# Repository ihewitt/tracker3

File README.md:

# Tracker III.2
A BG96 and NRF52840 based GPS tracker

The history for this design can be found on a series of posts: [Tracking running](https://blog.ivor.org/2020/10/tracking-running-part-2.html) [RAK track](https://blog.ivor.org/2022/02/between-rak-and-sweet-place.html) [Tracker two](https://blog.ivor.org/2022/03/trackertwo.html), the full details for this build are at [T3 Rise of the machines](https://blog.ivor.org/2024/08/t3-rise-of-machines.html)

Latest schematic [here](schematic.pdf), component layout [here](layout.pdf), Bill of materials [here](tracker-bom.csv)

Main functional features on the board are highlighted here:

### USB connection
I changed to a USB-C connector, and the USB connection can be switched between the NRF and BG96 chips, most of the time the NRF will be useful but if you need/want to diagnose the GPS data directly or update the BG96 firmware then you can move jumpers.

### Charger
I changed the charger design to include a load share design and a power regulator with a "reverse current" protection shown on the schematic:

When USB power is applied and the TP4056 starts charging, the MOSFET IC2 detaches the battery from the load and the power to the board is taken from the regulator U9.
When the USB power is removed and the battery (VBAT_IN) is the source then the MOSFET lets the power run through to VBAT_OUT directly, the reverse current protection on U9 prevents it returning to the 5v line.

### Regulators
The board internally runs all devices and data lines at 1.8v but level shifts these for external interfacing to 3.3v.

### IO Ports
Two qwiik compatible connectors provide 3.3v I2C and general purpose IO lines.

### Fuel Gauge
A MAX17048 fuel gauge chip is included to give an accurate and reliable power level info.

### Flash
Onboard 8Gb Flash module, I'm still on the fence whether to replace this with an SDcard slot instead.

### Temp & Humidity
Since I had a space on the board and it was next to the I2C lines, I changed my mind and decided to include a SHTC3 temperature and humidity chip. I found the temperature in tracker2 wasn't particularly useful so instead used an external ANT sensor, but the humidity was handy.

### Button connectors
Four GPIO lines are exposed alongside a ground line to make it easy to add a set of buttons.

# Render
The render view in KiCad is handy to check the layout looks sane and makes sense:

A picture of a nearly final prototype up and running:

## Build Notes
The build is a single sided board so quite straightforward to manufacture, although there are a few options to make it simpler.

Firstly optional parts, the fuel gauge can be omitted just skip U4 and C17, the pull-ups are still needed though for working I2C.
Similarly the temperature sensor can be skipped, omit U10 and C35.
The flash isn't absolutely necessary, but it's an easy to solder part and it's really quite useful.
The entire charge circuit can be omitted if preferred and the battery charged externally, but again these aren't complicated parts to solder. 

Just skip the parts marked in green and connect VBAT_IN to VBAT_OUT (in red)

Another option is to use a BG95 instead of the BG96, since they are software and pin compatible, the BG95 was considerably cheaper for a while although prices seem to have returned to sanity now.
The downside of the BG95 is that it can't operate GPS and GSM simultaneously, not a huge issue with a 1 or 5 minute upload.

### Difficult parts
Next up, difficult parts to solder.... the fuel gauge U4, and the ESD's U2 and U5 have very close contacts, these can bridge even with hotplate soldering so need inspecting although the pins can be easily fixed with the touch of a fine soldering iron since the pins are visible at the edges. Similary the USB-C socket can be trouble and needs inspection.

### Soldering
It's a good idea to use low temperature solder since a full temperature reflow will also reflow the internals of the BG96 and Holyiot modules. Another possibility would be to get the board manufactured by someone else (or flowed yourself) in two stages, initially just all the components *except* the two modules using standard temperature solder. Then after the board is manufactured, apply low temp paste for the BG96 and Holyiot for a second low-temp reflow.

### Software
As a starting point the software for the "RAKtrack" can be used after changing the pin numbers (the Pin numbers for v3 are in [gpiopins.h](gpiopins.h)). When the IVRtrack code is polished I'll update and add to this github also. 

For RAK track, the website server software is [here](https://github.com/ihewitt/gps-server). and the firmware for the rak board is [here](https://github.com/ihewitt/raktrack).

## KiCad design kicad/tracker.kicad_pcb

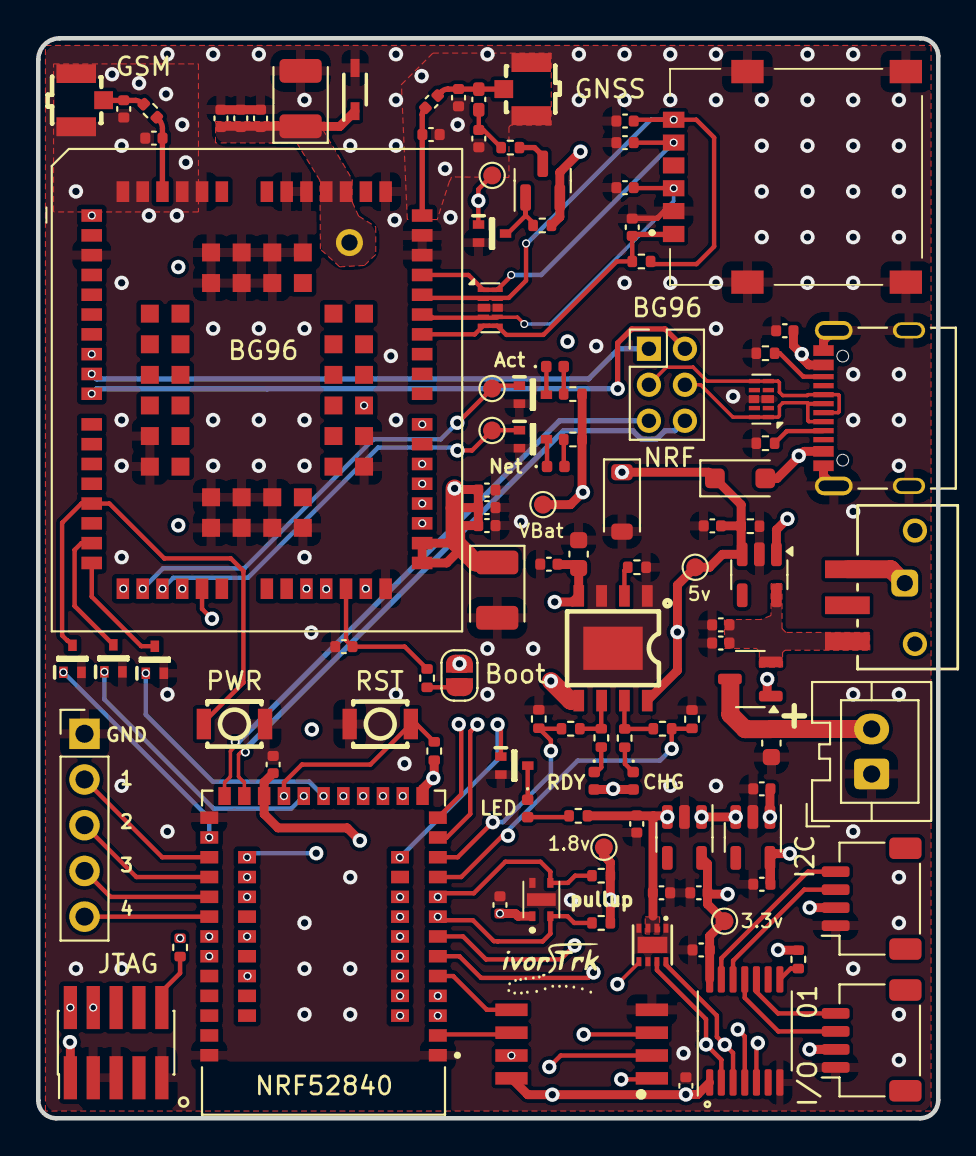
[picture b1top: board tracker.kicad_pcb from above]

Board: 4 copper layers, 50.0 x 60.0 mm, 111 parts (0 on the bottom side), 89 nets.

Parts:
ANT1, ANT2: U.FL-R-SMT-1_10_; RF-SMD_FRF05002-JSS103M
C1: 4.7uF; C_0402_1005Metric
C2: 10nF; C_0402_1005Metric
C3, C13, C14, C17, C18, C19, C29, C30, C31, C32, C33, C35: 0.1uF; C_0402_1005Metric
C4: 100pF; C_0402_1005Metric
C5, C6, C7, C11, C12: 33pF; C_0402_1005Metric
C8, C26, C27, C28: nc; C_0402_1005Metric
C9, C10: 10pF; C_0402_1005Metric
C15, C16: 100uF; CP_EIA-3528-21_Kemet-B
C20, C34: 10uF; C_0603_1608Metric
C21, C22, C23, C24, C25: 1uF; C_0402_1005Metric
D1: LED Orange; LED_0402_1005Metric
D2: LED Blue; LED_0402_1005Metric
D3: MBR140SFT1G; D_SOD-123F
D4: LBZT52B5V6T1G; D_SOD-123
D5: LED Red; LED_0402_1005Metric
D11: Green; LED_0402_1005Metric
D12: Red; LED_0402_1005Metric
H1, H4: Pad
IC1: IS25WP064A-JBLE; SOIC-8_L5.3-W5.3-P1.27-LS7.9-BL
IC2: DMP1045U-7; SOT-23-3
J1: Conn_01x05_Pin; PinHeader_1x05_P2.54mm_Vertical
J2, J6: I2C; JST_SH_SM04B-SRSS-TB_1x04-1MP_P1.00mm_Horizontal
J3: JTAG; PinHeader_2x05_P1.27mm_Vertical_SMD
J4: SMN-305; SMN305
J7: BAT_CON; JST_XA_B02B-XASK-1_1x02_P2.50mm_Vertical
J9: USBC; 12402012E212A
JP2: USB Select; PinHeader_2x03_P2.00mm_Vertical
L1: 47nh; L_0402_1005Metric_Pad0.77x0.64mm_HandSolder
Q1, Q5, Q6, Q7, Q8, Q9: DTC043ZEBTL; SOTFL50P160X85-3N
Q10: DTC143ZEBTL; SOTFL50P160X85-3N
Q11: IRLML6401; SOT-23
R1, R3, R4, R10, R16, R17: 10k; R_0402_1005Metric
R2, R9, R12, R13: 4.7k; R_0402_1005Metric
R5, R6: 5.1k; R_0402_1005Metric
R7: 100k; R_0402_1005Metric
R8, R15, R23, R24: 1k; R_0402_1005Metric
R11: 10; R_0402_1005Metric
R14, R18: 0; R_0402_1005Metric
R19, R20: 2k; R_0402_1005Metric
R22: 1.2k; R_0402_1005Metric
SW1: PWR; KEY-SMD_B3U-1000PM
SW2: RESET; KEY-SMD_B3U-1000PM
SW3: SW_SPDT; SW3_CSS-1210TB_NDC
TP1: TestPoint_2Pole; SolderJumper-2_P1.3mm_Open_RoundedPad1.0x1.5mm
TP3, TP4, TP5, TP6, TP7, TP8, TP9: TestPoint; TestPoint_Pad_D1.0mm
U1: HOLYIOT-18010-NRF52840; XCVR_HOLYIOT-18010-NRF52840
U2, U5: D3V3XA4B10LP; Diodes_UDFN-10_1.0x2.5mm_P0.5mm
U3: BG96; Quectel_BG96
U4: MAX17048; DFN-8_L2.0-W2.0-P0.50-BL-EP
U6: TP4056; ESOP-8_L4.9-W3.9-P1.27-LS6.0-BL-EP
U7: AP2127K-3.3; SOT-23-5
U8: AP2127K-1.8; SOT-23-5
U9: RP173N421B; SOT-23-5
U10: SHTC3
U11: TXS0104PWR; TSSOP-14_4.4x5mm_P0.65mm
Z1: MM3Z5V1ST1G; SOD2512X110N

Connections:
+3.3V: C23.1, C30.1, J2.2, J6.2, TP5.1, U7.5 (VOUT), U11.14 (VCCB)
+5V: C19.2, C32.2, C34.1, D3.1 (K), D4.1 (K), D11.2 (A), D12.2 (A), IC2.1 (G), R7.1, TP6.1, U3.8 (USB_VBUS), U6.4 (VCC), U6.8 (CE), U9.1 (VIN), U9.3 (EN)
BAT_ALRT: U1.40 (P0.25), U4.5 (~ALRT)
BG96_AP_READY: U1.49 (P0.24), U3.19 (AP_READY)
BG96_CTS: U1.15 (P0.07), U3.36 (CTS)
BG96_DTR: U1.16 (P1.09), U3.30 (DTR)
BG96_NETLIGHT: Q9.1 (B), TP8.1, U3.21 (NETLIGHT)
BG96_PSM: U1.43 (P0.27), U3.1 (PSM_IND)
BG96_PWRKEY: Q8.1 (B), U1.26 (P0.22)
BG96_PWRKEY_N: Q8.3 (C), SW1.2 (B), U3.15 (PWRKEY)
BG96_RESET: Q7.1 (B), U1.20 (P0.19)
BG96_RESET_N: Q7.3 (C), U3.17 (~RESET)
BG96_RI: U1.18 (P0.23), U3.39 (RI)
BG96_RTS: U1.17 (P0.12), U3.37 (RTS)
BG96_RX: U1.12 (P0.04), U3.34 (RXD)
BG96_RX2: U1.44 (P0.08), U3.23 (DBG_TXD)
BG96_RX3: U1.54 (P0.13), U3.28 (UART3_RXD)
BG96_STATUS: Q1.1 (B), TP7.1, U1.41 (P0.11), U3.20 (STATUS)
BG96_TX: U1.13 (P0.05), U3.35 (TXD)
BG96_TX2: U1.42 (P1.08), U3.22 (DBG_RXD)
BG96_TX3: U1.55 (P0.16), U3.27 (UART3_TXD)
BG96_USB+: JP2.1, U3.9 (USB_DP)
BG96_USB-: JP2.2, U3.10 (USB_DM)
BG96_W_DISABLE: Q6.1 (B), U1.19 (P0.21)
BG96_W_DISABLE_N: Q6.3 (C), U3.18 (W_DISABLE#)
BUT1: J1.2, U1.27 (P1.00)
BUT2: J1.3, U1.28 (P1.03)
BUT3: J1.4, U1.29 (P1.01)
BUT4: J1.5, U1.30 (P1.02)
CHG_DET: R15.2, R19.1, U1.10 (P0.30)
D+: J9.A6 (D+_A), J9.B6 (D+_B), JP2.3, U5.5, U5.6 (NC)
D-: J9.A7 (D-_A), J9.B7 (D-_B), JP2.4, U5.1, U5.10 (NC)
GND: ANT1.2, ANT1.3, ANT2.2, ANT2.3, C1.2, C2.2, C3.1, C5.1, C6.1, C7.1, C8.1, C9.2, C10.2, C11.2, C12.2, C13.2, C14.2, C15.2, C16.2, C17.2, C18.2, C19.1, C20.1, C21.2, C22.2, C23.2, C24.2, C25.2, C26.1, C27.2, C28.2, C29.1, C30.2, C31.1, C32.1, C33.1, C34.2, C35.2, D4.2 (A), IC1.4 (GND), J1.1, J2.1, J3.3 (GND), J3.5 (GND), J3.9 (GNDDetect), J4.C5 (GND), J4.MP1, J4.MP2, J4.MP3, J4.MP4, J6.1, J7.1, J9.A1_B12 (GND), J9.B1_A12 (GND), J9.SH1 (SHIELD), J9.SH2 (SHIELD), J9.SH3 (SHIELD), J9.SH4 (SHIELD), Q1.2 (E), Q5.2 (E), Q6.2 (E), Q7.2 (E), Q8.2 (E), Q9.2 (E), Q10.2 (E), R5.2, R6.2, R7.2, R19.2, R20.2, R22.2, SW1.1 (A), SW2.1 (A), U1.1 (GND), U1.25 (GND), U1.37 (GND), U2.3 (VSS), U2.8 (VSS), U3.3 (GND), U3.31 (GND), U3.47 (USIM_GND), U3.48 (GND), U3.50 (GND), U3.54 (GND), U3.55 (GND), U3.58 (GND), U3.59 (GND), U3.61 (GND), U3.62 (GND), U3.67 (GND), U3.68 (GND), U3.69 (GND), U3.70 (GND), U3.71 (GND), U3.72 (GND), U3.73 (GND), U3.74 (GND), U3.79 (GND), U3.80 (GND), U3.81 (GND), U3.82 (GND), U3.89 (GND), U3.90 (GND), U3.91 (GND), U3.100 (GND), U3.101 (GND), U3.102 (GND), U4.1 (CTG), U4.4 (GND), U4.6 (QSTRT), U4.9 (EP), U5.3 (VSS), U5.8 (VSS), U6.1 (TEMP), U6.3 (GND), U6.9 (EP), U7.2 (GND), U8.2 (GND), U9.2 (GND), U10.4 (VSS), U10.5 (PAD), U11.7 (GND), Z1.2 (A)
GPS_EN: Q10.1 (B), TP9.1, U1.53 (P0.14)
IO0: J6.3, U11.11 (B3)
IO1: J6.4, U11.10 (B4)
NRF_IO0: U1.7 (P0.02), U11.4 (A3)
NRF_IO1: U1.6 (P0.03), U11.5 (A4)
NRF_LED1: Q5.1 (B), U1.46 (P0.26)
NRF_RESET: R4.2, R14.2, SW2.2 (B), U1.21 (P0.18)
NRF_SCL: R3.2, U1.8 (P0.28), U4.7 (SCL), U10.2 (SCL), U11.2 (A1)
NRF_SDA: R1.2, U1.9 (P0.29), U4.8 (SDA), U10.3 (SDA), U11.3 (A2)
NRF_USB+: JP2.5, U1.24 (D+)
NRF_USB-: JP2.6, U1.23 (D-)
unnamed: ANT1.1, C8.2, R18.1
unnamed: ANT2.1, C4.1, C28.1, L1.2
unnamed: C3.2, L1.1, R11.1
unnamed: D1.2 (A), R9.1
unnamed: D1.1 (K), Q5.3 (C)
unnamed: D2.2 (A), R12.1
unnamed: D2.1 (K), Q9.3 (C)
unnamed: D5.2 (A), R13.1
unnamed: D5.1 (K), Q1.3 (C)
unnamed: D11.1 (K), R23.2
unnamed: D12.1 (K), R24.2
unnamed: J3.10 (~RESET), R14.1
unnamed: J9.A5 (CC1_A), R5.1
unnamed: J9.B5 (CC1_B), R6.1
unnamed: Q10.3 (C), Q11.1 (G), R16.2
unnamed: R17.2, TP1.1
unnamed: C4.2, C27.1, U3.49 (ANT_GNSS)
unnamed: C26.2, R18.2, U3.60 (ANT_MAIN)
unnamed: TP1.2, U3.75 (USB_BOOT)
unnamed: R22.1, U6.2 (PROG)
unnamed: R15.1, R24.1, U6.7 (~CHRG)
unnamed: R8.1, R23.1, U6.6 (~STDBY)
unnamed: R2.1, U11.8 (OE)
QSPI_CLK: IC1.6 (SCK), U1.2 (P1.11)
QSPI_CS: IC1.1 (CE#), U1.3 (P1.10)
QSPI_DIO0: IC1.5 (SI), U1.5 (P1.15)
QSPI_DIO1: IC1.2 (SO), U1.38 (P1.14)
QSPI_DIO2: IC1.3 (WP#), U1.4 (P1.13)
QSPI_DIO3: IC1.7 (HOLD#), U1.39 (P1.12)
RDY_SET: R8.2, R20.1, U1.11 (P0.31)
SCL: J2.4, U11.13 (B1)
SDA: J2.3, U11.12 (B2)
SIM_CLK: C6.2, J4.C3 (CLK), U2.1, U2.10 (NC), U3.46 (USIM_CLK)
SIM_DATA: C7.2, J4.C7 (I/O), R10.2, U2.2, U2.9 (NC), U3.45 (USIM_DATA)
SIM_RST: C5.2, J4.C2 (RST), U2.4, U2.7 (NC), U3.44 (USIM_RST)
SIM_VDD: C2.1, J4.C1 (VCC), R10.1, U2.5, U2.6 (NC), U3.43 (USIM_VDD)
SWDCLK: J3.4 (SWCLK/TCK), U1.31 (SWDCLK)
SWDIO: J3.2 (SWDIO/TMS), U1.32 (SWDIO)
VBAT: C9.1, C10.1, C11.1, C12.1, C13.1, C14.1, C15.1, C16.1, C17.1, C22.1, C24.1, H1.1, H4.1, Q11.2 (S), R9.2, R12.2, R13.2, R16.1, SW3.3, TP3.1, U3.32 (VBAT_BB), U3.33 (VBAT_BB), U3.52 (VBAT_RF), U3.53 (VBAT_RF), U4.2 (CELL), U4.3 (VDD), U7.1 (VIN), U7.3 (EN), U8.1 (VIN), U8.3 (EN), Z1.1 (K)
VBAT_IN: C20.2, IC2.3 (D), J7.2, U6.5 (BAT)
VBAT_OUT: C21.1, C33.2, IC2.2 (S), SW3.1, U9.5 (VOUT)
VBUS: C1.1, C18.1, D3.2 (A), J9.A4_B9 (VBUS), J9.B4_A9 (VBUS), U1.22 (VBUS)
VCC_GPS: Q11.3 (D), R11.2
VDD_EXT: C29.2, R17.1, U3.29 (VDD_EXT)
VDD_NRF: C25.1, C31.2, C35.1, IC1.8 (VCC), J3.1 (VTref), R1.1, R2.2, R3.1, R4.1, TP4.1, U1.14 (VDD_NRF), U8.5 (VOUT), U10.1 (VDD), U11.1 (VCCA)

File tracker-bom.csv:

Reference,Value,Qty,MRF,Digikey
"ANT1,ANT2",U.FL-R-SMT-1_10_,2,U.FL-R-SMT(10),H9161CT-ND
C1,4.7uF,1,GRM155R60J475ME47J,490-GRM155R60J475ME47JCT-ND
C2,10nF,1,CC0402KRX7R6BB103,311-1703-1-ND
"C3,C13,C14,C17,C18,C19,C29,C30,C31,C32,C33",0.1uF,11,CL10B104KB8NNWC,1276-1935-1-ND
C4,100pF,1,CC0402JRNPO9BN101,311-1024-1-ND
"C5,C6,C7,C11,C12",33pF,5,GRM1555C1H330JA01D,490-5936-1-ND
"C9,C10",10pF,2,GRM1555C1H100JA01D,490-5921-1-ND
"C15,C16",100uF,2,TAJA107K004RNJ,478-8876-1-ND
"C20,C34",10uF,2,CM105X5R106K16AT,478-CM105X5R106K16ATCT-ND
"C21,C22,C23,C24,C25",1uF,5,CL05A105KQ5NNNC,1276-1010-1-ND
D1,LED Orange,1,B2841UD--20D000614U1930,3147-B2841UD--20D000614U1930CT-ND
D2,LED Blue,1,B2841NB--20C001414U1930,3147-B2841NB--20C001414U1930CT-ND
D3,MBR140SFT1G,1,MBR140SFT1G,MBR140SFT1GOSTR-ND
D4,LBZT52B5V6T1G,1,BZT52B5V6-HE3_A-08,112-BZT52B5V6-HE3_A-08TR-ND
"D5,D12",LED Red,2,B2841URO-20C001114U1930,3147-B2841URO-20C001114U1930CT-ND
D11,Green,1,B1811NG--05D001013U1930,3147-B1811NG--05D001013U1930CT-ND
IC1,IS25WP064A-JBLE,1,IS25WP064A-JBLE,706-1590-ND
IC2,DMP1045U-7,1,DMP1045U-7,DMP1045U-7DITR-ND
"J2,J6",I2C,2,SM04B-SRSS-TB,455-SM04B-SRSS-TBCT-ND
J3,JTAG,1,FTSH-105-01-F-DV,SAM8795-ND
J4,SMN-305,1,NSIM-2-C,2223-NSIM-2-CCT-ND
J7,BAT_CON,1,B02B-XASK-1N,455-B02B-XASK-1N-ND
J9,USBC,1,12402012E212A,664-12402012E212ATR-ND
JP2,USB Select,1,PR20C03VBDN,1849-1000-ND
L1,47nh,1,7447860147,732-7447860147CT-ND
"Q1,Q5,Q6,Q7,Q8,Q9",DTC043ZEBTL,6,DTC043ZEBTL,DTC043ZEBTLCT-ND
Q10,DTC143ZEBTL,1,DTC143ZEBTL,DTC143ZEBTLCT-ND
Q11,IRLML6401,1,IRLML6401TRPBF,IRLML6401PBFCT-ND
"R1,R3,R4,R10,R16,R17",10k,6,RC0603FR-0710KL,311-10.0KHRCT-ND
"R2,R9,R12,R13",4.7k,4,RC0402FR-074K7L,311-4.7KLRCT-ND
"R5,R6",5.1k,2,ERJ-2GEJ512X,P5.1KJTR-ND
R7,100k,1,RC0402FR-07100KL,311-100KLRTR-ND
"R8,R15,R23,R24",1k,4,RC0402FR-071KL,311-1.00KLRCT-ND
R11,10,1,RC0402FR-0710RL,311-10.0LRCT-ND
"R14,R18",0,2,RMCF0402ZT0R00,RMCF0402ZT0R00CT-ND
"R19,R20",2k,2,ERJ-2RKF2001X,P2.00KLTR-ND
R22,1.2k,1,RMCF0402JT1K20,RMCF0402JT1K20CT-ND
"SW1,SW2","PWR,RESET",2,B3U-1000PM,39-B3U-1000PMTR-ND
SW3,SW_SPDT,1,CSS-1210TB,563-1091-1-ND
U1,HOLYIOT-18010,1,,
"U2,U5",D3V3XA4B10LP,2,D3V3XA4B10LP-7,31-D3V3XA4B10LP-7CT-ND
U3,BG96,1,,
U4,MAX17048,1,MAX17048G+T10,MAX17048G+T10TR-ND
U6,TP4056,1,,
U7,AP2127K-3.3,1,AP2127K-3.3TRG1,AP2127K-3.3TRG1DICT-ND
U8,AP2127K-1.8,1,AP2127K-1.8TRG1,AP2127K-1.8TRG1DICT-ND
U9,RP173N421B,1,RP173N421B-TR-FE,RP173N421B-TR-FE
U11,TXS0104PWR,1,TXS0104EPWR,296-20697-1-ND
Z1,MM3Z5V1ST1G,1,MM3Z5V1ST1G,MM3Z5V1ST1GOSCT-ND

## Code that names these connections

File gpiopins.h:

#define LED_PIN         NRF_GPIO_PIN_MAP(0, 26)
#define CHG_DET         NRF_GPIO_PIN_MAP(0, 30) // TP4056 CHRG
#define BAT_RDY         NRF_GPIO_PIN_MAP(0, 31) // TP4056 STDBY
#define BAT_ALRT        NRF_GPIO_PIN_MAP(0, 25) // Fuel Gauge ALRT
#define BUT1            NRF_GPIO_PIN_MAP(1, 0)
#define BUT2            NRF_GPIO_PIN_MAP(1, 3)
#define BUT3            NRF_GPIO_PIN_MAP(1, 1)
#define BUT4            NRF_GPIO_PIN_MAP(1, 2)
#define PIN_IO0         NRF_GPIO_PIN_MAP(0, 2)  // Qwiic 2
#define PIN_IO1         NRF_GPIO_PIN_MAP(0, 3)
#define SCL_PIN         NRF_GPIO_PIN_MAP(0, 28) // Qwiic 1
#define SDA_PIN         NRF_GPIO_PIN_MAP(0, 29)

#define GPS_TX2_PIN     NRF_GPIO_PIN_MAP(1, 8)
#define GPS_RX2_PIN     NRF_GPIO_PIN_MAP(0, 8)
#define GPS_TX3_PIN     NRF_GPIO_PIN_MAP(0, 16) // GPS stream
#define GPS_RX3_PIN     NRF_GPIO_PIN_MAP(0, 13)
#define GPS_TXD_PIN     NRF_GPIO_PIN_MAP(0, 5)  // GSM io 
#define GPS_RXD_PIN     NRF_GPIO_PIN_MAP(0, 4)
#define GPS_CTS_PIN     NRF_GPIO_PIN_MAP(0, 7)
#define GPS_RTS_PIN     NRF_GPIO_PIN_MAP(0, 12)

#define GSM_EN_PIN      NRF_GPIO_PIN_MAP(0, 14) // antenna power
#define GSM_RESET_PIN   NRF_GPIO_PIN_MAP(0, 19)
#define GSM_PWRKEY_PIN  NRF_GPIO_PIN_MAP(0, 22)
#define GSM_DISABLE_PIN NRF_GPIO_PIN_MAP(0, 21) // aka airplane mode
#define GSM_STATUS      NRF_GPIO_PIN_MAP(0, 11)
#define GSM_AP_READY    NRF_GPIO_PIN_MAP(0, 24)

#define PIN_RESET       NRF_GPIO_PIN_MAP(0, 18) // nrf reset line 

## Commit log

2024-08-26 Initial upload
2024-08-26 Update docs
2024-08-26 Add build notes
2024-08-26 Add pcb layout
2024-08-26 Add BOM file with digikey references
2024-08-27 Added gpio pin info and bg95 comments
2024-08-30 Update README.md
    Add missing links
